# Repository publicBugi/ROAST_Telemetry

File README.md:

# ROAST_Telemetry
STM32 Telemetry project for DTU Roadrunners solar car team for the World Solar Challenge.

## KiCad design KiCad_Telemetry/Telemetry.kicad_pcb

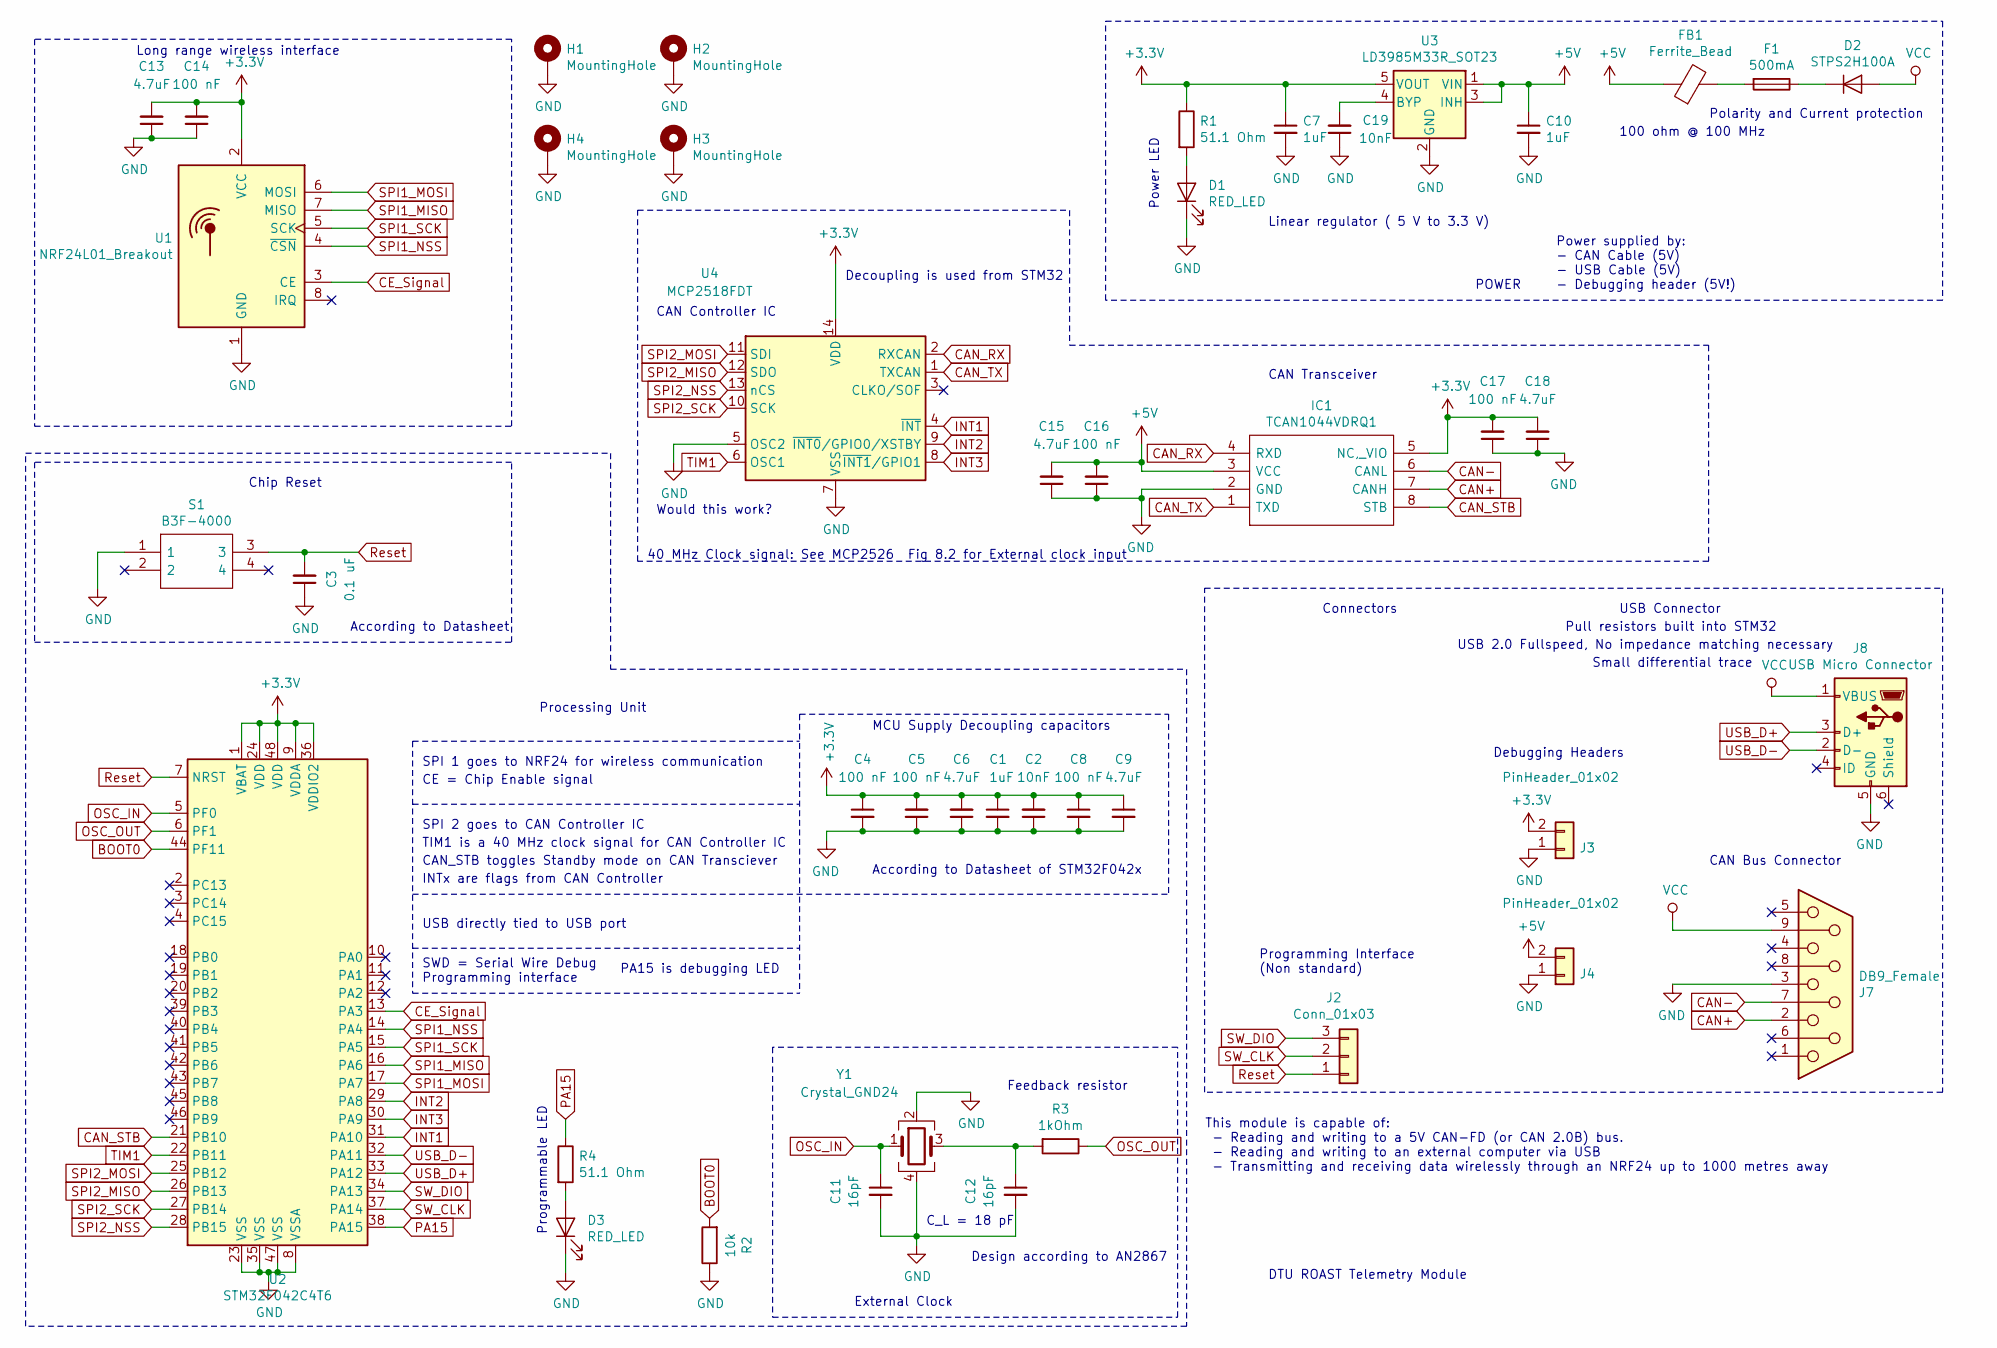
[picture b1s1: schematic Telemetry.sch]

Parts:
C1, C7, C10: 1uF; C_0402_1005Metric; MouserNO 81-GRT155R61E105KE1D
C2, C19: 10nF; C_0402_1005Metric; MouserNO 80-C0402C103J3RAUTO
C3: 0.1 uF; C_0402_1005Metric; MouserNO 81-GRM155C71H104JE9D
C4, C5, C8, C14, C16, C17: 100 nF; C_0402_1005Metric; MouserNO 81-GRM155C71H104JE9D
C6, C9, C13, C15, C18: 4.7uF; C_0402_1005Metric; MouserNO 603-CC0402KR5R6BB475
C11, C12: 16pF; C_0402_1005Metric; MouserNO 81-GCM1555C1H160JA6D
D1, D3: RED_LED; LED_0603_1608Metric_Pad1.05x0.95mm_HandSolder; MouserNO 720-KRDELPS122A5163
D2: STPS2H100A; D_SMA_Handsoldering; MouserNO 511-STPS2H100A
F1: 500mA; Fuse_0603_1608Metric_Pad1.05x0.95mm_HandSolder; MouserNO 581-F0603E0R50FSTR
FB1: Ferrite_Bead; L_0603_1608Metric_Pad1.05x0.95mm_HandSolder
H1, H2, H3, H4: MountingHole; MountingHole_3.5mm_Pad_Via
IC1: TCAN1044VDRQ1; SOIC-8_3.9x4.9mm_P1.27mm; MouserNO 595-TCAN1044VDRQ1
J2: Conn_01x03; PinHeader_1x03_P2.54mm_Vertical; MouserNO 855-M20-9990345
J3, J4: PinHeader_01x02; PinHeader_1x02_P2.54mm_Vertical; MouserNO 855-M20-9730245
J7: DB9_Female; DSUB-9_Female_Horizontal_P2.77x2.84mm_EdgePinOffset4.94mm_H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; MouserNO 649-LD09S33E4GX00LF
J8: USB Micro Connector; USB_Micro-B_Molex_47346-0001; MouserNO 538-105017-0001
R1, R4: 51.1 Ohm; R_0603_1608Metric_Pad1.05x0.95mm_HandSolder; MouserNO 754-RR0816Q-51R1D69R
R2: 10k; R_0603_1608Metric_Pad1.05x0.95mm_HandSolder; MouserNO 754-RR0816P-912D
R3: 1kOhm; R_0402_1005Metric; MouserNO 603-RT0402FRE071KL
S1: B3F-4000; Manufacturer_Part_Number B3F-4000; MouserNO 653-B3F-4000
U1: NRF24L01_Breakout; NRF24L01PALNA_THT; MouserNO None
U2: STM32F042C4T6; LQFP-48_7x7mm_P0.5mm; MouserNO 511-STM32F042C4T6
U3: LD3985M33R_SOT23; SOT-23-5
U4: MCP2518FDT; SOIC-14_3.9x8.7mm_P1.27mm; MouserNO 579-MCP2518FDT-H/SL
Y1: Crystal_GND24; Crystal_SMD_Abracon_ABM3B-4Pin_5.0x3.2mm; MouserNO 815-M3BAIG-8-1ZT

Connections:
+3V3: C1.1, C2.2, C4.1, C5.2, C6.2, C7.1, C8.1, C9.1, C13.2, C14.2, C17.2, C18.2, IC1.5 (NC,_VIO), J3.2, R1.1, U1.2 (VCC), U2.1 (VBAT), U2.9 (VDDA), U2.24 (VDD), U2.36 (VDDIO2), U2.48 (VDD), U3.5 (VOUT), U4.14 (VDD)
+5V: C10.1, C15.2, C16.2, FB1.1, IC1.3 (VCC), J4.2, U3.1 (VIN), U3.3 (INH)
BOOT0: R2.2, U2.44 (PF11)
CAN+: IC1.7 (CANH), J7.2
CAN-: IC1.6 (CANL), J7.7
CAN_RX: IC1.4 (RXD), U4.2 (RXCAN)
CAN_STB: IC1.8 (STB), U2.21 (PB10)
CAN_TX: IC1.1 (TXD), U4.1 (TXCAN)
CE_Signal: U1.3 (CE), U2.13 (PA3)
GND: C1.2, C2.1, C3.1, C4.2, C5.1, C6.1, C7.2, C8.2, C9.2, C10.2, C11.2, C12.2, C13.1, C14.1, C15.1, C16.1, C17.1, C18.1, C19.1, D1.1 (K), D3.1 (K), H1.1, H2.1, H3.1, H4.1, IC1.2 (GND), J3.1, J4.1, J7.3, J8.5 (GND), R2.1, S1.1, U1.1 (GND), U2.8 (VSSA), U2.23 (VSS), U2.35 (VSS), U2.47 (VSS), U3.2 (GND), U4.5 (OSC2), U4.7 (VSS), Y1.2, Y1.4
INT1: U2.31 (PA10), U4.4 (~INT)
INT2: U2.29 (PA8), U4.9 (~INT0~/GPIO0/XSTBY)
INT3: U2.30 (PA9), U4.8 (~INT1~/GPIO1)
unnamed: C12.1, R3.2, Y1.3
unnamed: C19.2, U3.4 (BYP)
unnamed: D1.2 (A), R1.2
unnamed: D2.1 (K), F1.1
unnamed: D3.2 (A), R4.2
unnamed: F1.2, FB1.2
OSC_IN: C11.1, U2.5 (PF0), Y1.1
OSC_OUT: R3.1, U2.6 (PF1)
PA15: R4.1, U2.38 (PA15)
Reset: C3.2, J2.1, S1.3, U2.7 (NRST)
SPI1_MISO: U1.7 (MISO), U2.16 (PA6)
SPI1_MOSI: U1.6 (MOSI), U2.17 (PA7)
SPI1_NSS: U1.4 (~CSN), U2.14 (PA4)
SPI1_SCK: U1.5 (SCK), U2.15 (PA5)
SPI2_MISO: U2.26 (PB13), U4.12 (SDO)
SPI2_MOSI: U2.25 (PB12), U4.11 (SDI)
SPI2_NSS: U2.28 (PB15), U4.13 (nCS)
SPI2_SCK: U2.27 (PB14), U4.10 (SCK)
SW_CLK: J2.2, U2.37 (PA14)
SW_DIO: J2.3, U2.34 (PA13)
TIM1: U2.22 (PB11), U4.6 (OSC1)
USB_D+: J8.3 (D+), U2.33 (PA12)
USB_D-: J8.2 (D-), U2.32 (PA11)
VCC: D2.2 (A), J7.9, J8.1 (VBUS)

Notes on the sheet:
Chip Reset
Long range wireless interface
External Clock
Programmable LED
Power LED
C_L = 18 pF
MCU Supply Decoupling capacitors
Design according to AN2867
Feedback resistor
Processing Unit
SPI 1 goes to NRF24 for wireless communication
SPI 2 goes to CAN Controller IC
USB directly tied to USB port
TIM1 is a 40 MHz clock signal for CAN Controller IC
CAN_STB toggles Standby mode on CAN Transciever
INTx are flags from CAN Controller
SWD = Serial Wire Debug Programming interface
CE = Chip Enable signal
PA15 is debugging LED
According to Datasheet of STM32F042x
According to Datasheet
CAN Bus Connector
USB Connector
Pull resistors built into STM32
Debugging Headers
Programming Interface (Non standard)
Connectors
CAN Controller IC
CAN Transceiver
Polarity and Current protection
Linear regulator ( 5 V to 3.3 V)
POWER
Power supplied by: - CAN Cable (5V) - USB Cable (5V) - Debugging header (5V!)
40 MHz Clock signal: See MCP2526 Fig 8.2 for External clock input
Would this work?
This module is capable of: - Reading and writing to a 5V CAN-FD (or CAN 2.0B) bus. - Reading and writing to an external computer via USB - Transmitting and receiving data wirelessly through an NRF24 up to 1000 metres away
Small differential trace
USB 2.0 Fullspeed, No impedance matching necessary
DTU ROAST Telemetry Module
Decoupling is used from STM32

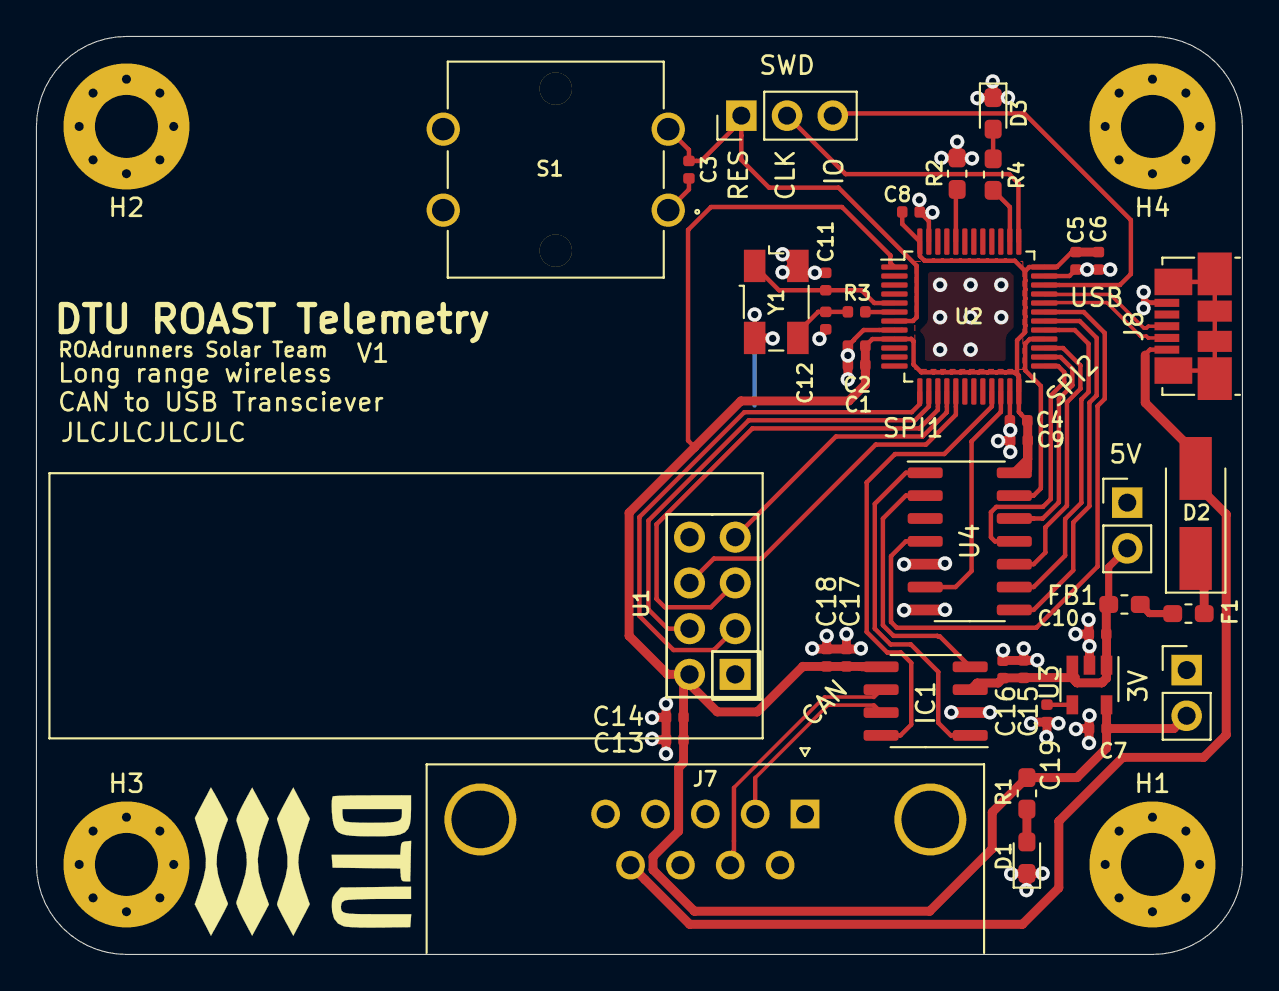
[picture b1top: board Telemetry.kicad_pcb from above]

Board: 2 copper layers, 67.0 x 51.0 mm, 44 parts (0 on the bottom side), 37 nets.

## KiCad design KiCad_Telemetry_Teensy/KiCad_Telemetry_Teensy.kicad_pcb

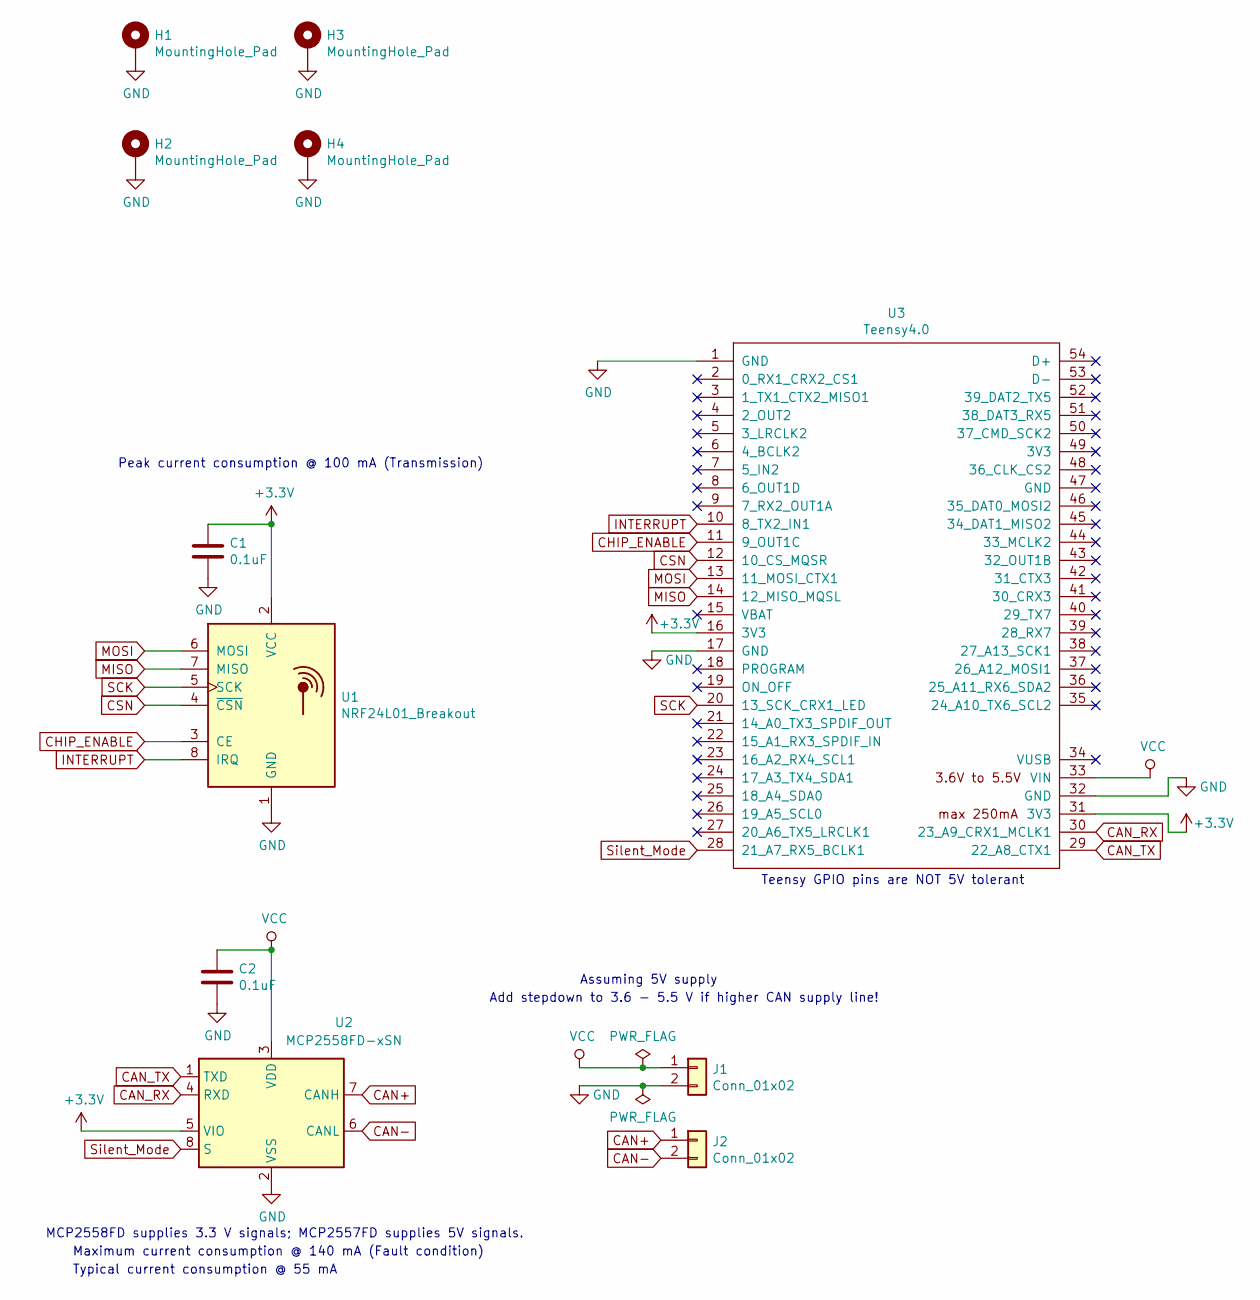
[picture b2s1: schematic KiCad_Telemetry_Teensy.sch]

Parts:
C1, C2: 0.1uF; C_0603_1608Metric_Pad1.05x0.95mm_HandSolder
H1, H2, H3, H4: MountingHole_Pad; MountingHole_3.2mm_M3_Pad_Via
J1, J2: Conn_01x02; PinHeader_1x02_P2.54mm_Vertical
U1: NRF24L01_Breakout; NRF24L01PALNA_THT
U2: MCP2558FD-xSN; SOIC-8_3.9x4.9mm_P1.27mm
U3: Teensy4.0; Teensy40

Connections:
+3V3: C1.2, U1.2 (VCC), U2.5 (VIO), U3.16 (3V3), U3.31 (3V3)
CAN+: J2.1, U2.7 (CANH)
CAN-: J2.2, U2.6 (CANL)
CAN_RX: U2.4 (RXD), U3.30 (23_A9_CRX1_MCLK1)
CAN_TX: U2.1 (TXD), U3.29 (22_A8_CTX1)
CHIP_ENABLE: U1.3 (CE), U3.11 (9_OUT1C)
CSN: U1.4 (~CSN), U3.12 (10_CS_MQSR)
GND: C1.1, C2.1, H1.1, H2.1, H3.1, H4.1, J1.2, U1.1 (GND), U2.2 (VSS), U3.1 (GND), U3.17 (GND), U3.32 (GND)
INTERRUPT: U1.8 (IRQ), U3.10 (8_TX2_IN1)
MISO: U1.7 (MISO), U3.14 (12_MISO_MQSL)
MOSI: U1.6 (MOSI), U3.13 (11_MOSI_CTX1)
SCK: U1.5 (SCK), U3.20 (13_SCK_CRX1_LED)
Silent_Mode: U2.8 (S), U3.28 (21_A7_RX5_BCLK1)
VCC: C2.2, J1.1, U2.3 (VDD), U3.33 (VIN)

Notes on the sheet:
Peak current consumption @ 100 mA (Transmission)
Maximum current consumption @ 140 mA (Fault condition)
Typical current consumption @ 55 mA
Assuming 5V supply
Add stepdown to 3.6 - 5.5 V if higher CAN supply line!
Teensy GPIO pins are NOT 5V tolerant
MCP2558FD supplies 3.3 V signals; MCP2557FD supplies 5V signals.

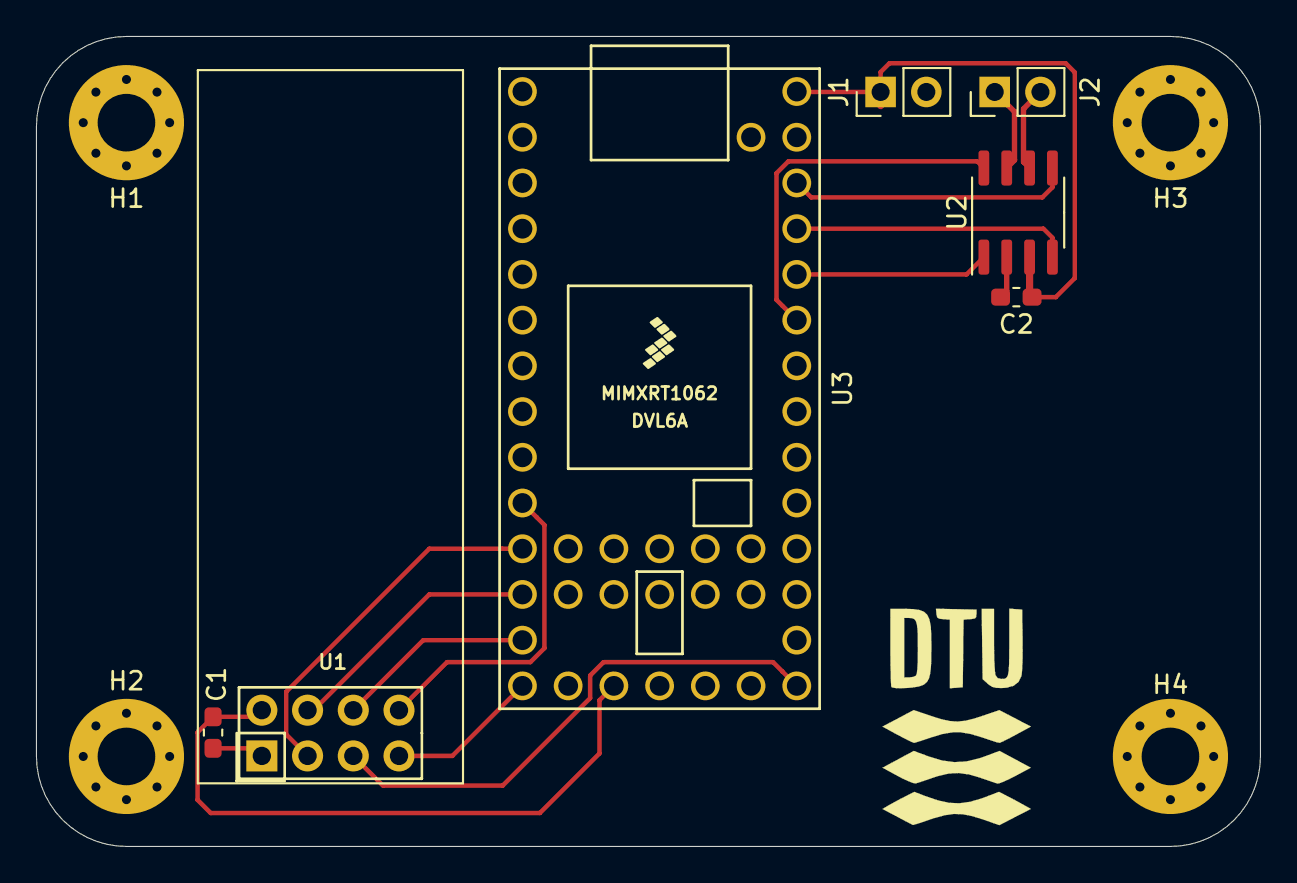
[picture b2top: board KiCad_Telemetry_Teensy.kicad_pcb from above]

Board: 2 copper layers, 68.0 x 45.0 mm, 11 parts (0 on the bottom side), 14 nets.

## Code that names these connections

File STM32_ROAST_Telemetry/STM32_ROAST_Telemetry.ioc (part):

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PA6.Mode=Full_Duplex_Master
PA7.Mode=Full_Duplex_Master
Mcu.UserName=STM32F042C6Tx
PA11.Mode=Device
PA3.GPIOParameters=GPIO_Label
PB15.Signal=SPI2_MOSI
PB13.Signal=SPI2_SCK
RCC.SYSCLKSource=RCC_SYSCLKSOURCE_HSI48
PA13.Signal=SYS_SWDIO
PA12.Signal=USB_DP
PA4.Mode=NSS_Signal_Hard_Output
PB9.Mode=Master
PF0-OSC_IN.Mode=HSE-External-Oscillator
PB14.Signal=SPI2_MISO
PA5.Signal=SPI1_SCK
board=custom
PB15.Mode=Full_Duplex_Master
PA14.Mode=Serial_Wire
PB14.Mode=Full_Duplex_Master
PA13.Mode=Serial_Wire
Mcu.Name=STM32F042C(4-6)Tx
PA0.Signal=GPIO_Output
PA4.Signal=SPI1_NSS
RCC.SYSCLKFreq_VALUE=48000000
Mcu.Package=LQFP48
PB9.Signal=CAN_TX
PA6.Signal=SPI1_MISO
PB12.Mode=NSS_Signal_Hard_Output
PA12.Mode=Device
PA11.Signal=USB_DM
PA14.Signal=SYS_SWCLK
PB8.Mode=Master
PB8.Signal=CAN_RX
PB13.Mode=Full_Duplex_Master
PF0-OSC_IN.Signal=RCC_OSC_IN
PF1-OSC_OUT.Mode=HSE-External-Oscillator
PB12.Signal=SPI2_NSS
PF1-OSC_OUT.Signal=RCC_OSC_OUT
PA3.GPIO_Label=SPI1_CE
PA3.Signal=GPIO_Output
PA5.Mode=Full_Duplex_Master
PA7.Signal=SPI1_MOSI

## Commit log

2020-04-20 Initial KiCad commit
2020-04-20 Initial STM32 project commit
2020-04-20 Added NRf24 Library
2020-04-27 Updated the schematic
2020-04-30 Completed footprint allocation and BOM
2020-05-11 Finished intial CAN-FD KiCad Design. Awaiting peer review
2020-05-15 Changed USB A to USB Micro port.
2020-05-25 Revised layout, Created GERBER and Drill Files. Finished BOM
2020-05-29 Minor edits; Generated gerber files
2020-05-29 Added Datasheets for components to repo
2020-06-03 Adding Receiver and Transiver Code
2020-06-03 Changes to NRF24 Connection
2020-06-04 Changes to Reciver File
2020-06-04 Added additional decoupling capacitors; Added Finished design sent to production
2020-06-05 Added h file, RF24-STM.h
2020-06-05 Added h file, RF24-STM.h
2020-06-08 Added Ferrite bead VBUS filtering Replaced LDO with component found on RS-Online (Same footprint, better parameters)
2020-06-11 Created a Teensy design Teensy design as a comparative analysis to the STM32 design.
2020-06-11 Fixed missing trace
2020-06-15 Updated final files for hand-in
